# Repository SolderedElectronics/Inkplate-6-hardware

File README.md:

# Inkplate 6 Open Source Hardware files

Open Source Hardware (OSH) files for e-paper display Inkplate 6 can be found in this repo. Inkplate 6 is a powerful, Wi-Fi enabled ESP32 based six-inch e-paper display – recycled from a Kindle e-reader. Its main feature is simplicity. Just plug in a USB cable, open Arduino IDE, and change the contents of the screen with few lines of code. Learn more about Inkplate 6 on [Crowd Supply](https://www.crowdsupply.com/e-radionica/inkplate-6) or [official website](https://inkplate.io).

### Versions:
- v1.0. first, original version shipped to backers in 2020 and manufactured until January 2021.

### Misc
Inkplate 6 is available for purchase via:
- [e-radionica.com](https://e-radionica.com/en/inkplate.html)
- [Crowd Supply](https://www.crowdsupply.com/e-radionica/inkplate-6)
- [Mouser](https://hr.mouser.com/Search/Refine?Keyword=inkplate)
- [Pimoroni](https://shop.pimoroni.com/products/inkplate-6)

For all questions and issues, please open an issue or thread on [our forums](http://forum.e-radionica.com/en/).
For sales & collaboration, please reach us via [e-mail](mailto:kontakt@e-radionica.com).

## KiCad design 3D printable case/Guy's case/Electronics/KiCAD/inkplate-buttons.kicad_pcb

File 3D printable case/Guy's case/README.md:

# InkPlate-6-Extended-Case

Find original Guy's work at [this repo](https://github.com/turgu1/InkPlate-6-Extended-Case).

This is a change to the current InkPlate-6 case to add a small electronic board with push buttons below the mainboard. To do it, I took the original design from e-Radionica and extended a side of it, so the original portion of the case remains unchanged. The `Mechanical CAD` folder contains the complete STEP format design as well as the STL files ready for 3D printing. The `Electronics` folder contains the Gerber files for the preparation of the pc-board, as well as the schematic in PDF. I have used **OnShape** and **KiCAD** to complete this project.

- For the STL files, dimensions are in millimeters. 
- Six buttons must be printed as well as the top and bottom casing. The buttons may have to be adjusted in size depending on the 3D printing results.
- The connection with the MCU23017 is done using wirewrap wires (or a flat cable) that are soldered at both ends using the following configuration (beware that the corresponding buttons numbers are inverted in the sequence):

```
   On the   |     On the     | Corresponding 
Buttons PCB | InkPlate Board |    Button
------------+----------------+---------------
            |                |
   Pin 1    |      GND       |
   Pin 2    |      GPB7      |      U6
   Pin 3    |      GPB6      |      U3
   Pin 4    |      GPB5      |      U5
   Pin 5    |      GPB4      |      U1
   Pin 6    |      GPB3      |      U4
   Pin 7    |      GPB2      |      U2
```

- The squared pad is pin 1.
- On the buttons' pc-board, there is no through-hole, just pads on the surface to solder the wires. This is to ensure that the board will remains flat at the bottom of it's location in the casing.
- The three touch pads on the InkPate-6 pc-board must be disabled, the corresponding signals from the MCU23017 must be diverted to the GPBx pin holes on the main pc-board. This is done by desoldering the current jumpers and soldering them back on the other side. They are located under the following labeling on the board: "Touch pads".
- The GPIOB I/O bits of the MCU23017 corresponding to the GPB2 through GPB7 pins must have their internal pull-up resistor enabled.
- The buttons' pc-board must be of a standard height (1.6 mm). This to ensure proper spacing for the printed buttons. The board must be 'glued' at the bottom of the main casing using two-sided scotch tape. An alternative would be using a very small amount of hot glue on the 4 corners on the top of the buttons' pc-board. This is to permit easy removal in case of problems. 
- The button switches' part number is C&K PTS526 SK15 SMTR2 LFS 5.2x5.2x1.5 mm. They are very common (For exemple, Mouser part # 611-PTS526SK15SMR2L, Digikey Part # CKN12221-1-ND, or other manufacturers equivalent). The 1.5 mm height is important to insure proper spacing for the printed buttons.

The original licensing from e-Radionica remains GPL-3 for their design as well as all supplied files in this project.

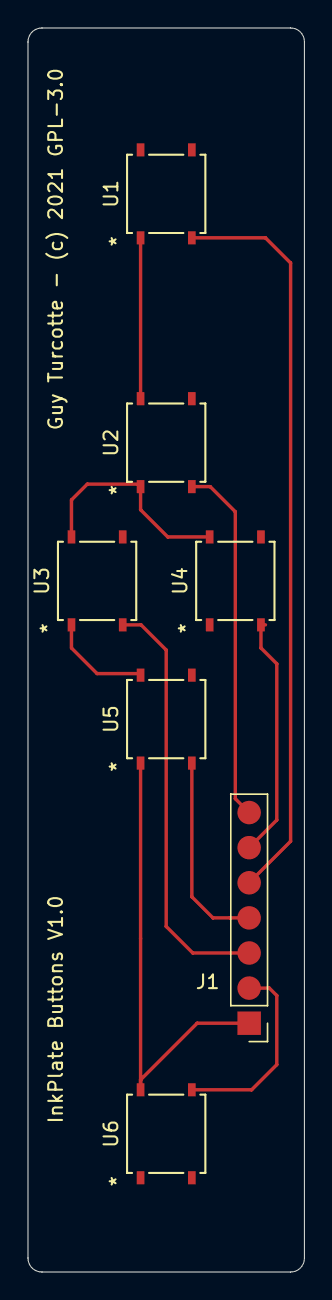
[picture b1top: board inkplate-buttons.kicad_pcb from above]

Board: 2 copper layers, 20.0 x 90.0 mm, 7 parts (0 on the bottom side), 10 nets.

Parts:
J1: J1; PinHeader_1x07_P2.54mm_Vertical
U1: U1; PTS526 SK15 SMTR2 LFS
U2: U2; PTS526 SK15 SMTR2 LFS
U3: U3; PTS526 SK15 SMTR2 LFS
U4: U4; PTS526 SK15 SMTR2 LFS
U5: U5; PTS526 SK15 SMTR2 LFS
U6: U6; PTS526 SK15 SMTR2 LFS

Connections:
unnamed: J1.1, U5.1, U6.2
unnamed: J1.2, U6.4
unnamed: J1.3, U3.3
unnamed: J1.4, U5.3
unnamed: J1.5, U1.3
unnamed: J1.6, U4.3
unnamed: J1.7, U2.3
unnamed: U1.1, U2.2
unnamed: U2.1, U3.2, U4.2
unnamed: U3.1, U5.2

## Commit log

2019-12-15 Add proto v4 schematics
2019-12-15 Add Proto v4 BOM
2019-12-15 Add prototype v4 gerbers
2020-01-16 Add technical drawings
2020-04-05 Upload production version files
    Uploaded and updated the new production files for Inkplate 6, including schematics, BOM and gereber files.
    Reoganised the repo a bit.
2020-05-10 Add the newest version
2020-05-18 add blend file
2020-07-31 Add IO to case
2020-10-19 STEP format case
2020-10-19 Add Fusion360 file
2021-02-09 Add Guy's case
2021-02-11 Add gitignore
2021-02-11 Add versioning folder
2021-02-16 Update README for Guy case

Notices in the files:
3D printable case/Guy's case/Electronics/KiCAD/inkplate-buttons.kicad_pcb:
Public Domain - GPL-3.0
Guy Turcotte - (c) 2021 GPL-3.0
parts and their libraries:
Copyright 2016 Accelerated Designs. All rights reserved.
